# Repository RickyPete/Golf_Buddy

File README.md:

# Golf_Buddy

The Golf Buddy is a universal digital golf scorecard that can be used on any course and can be set for either 9 or 18 holes games.

Inspiration for this project came from often loosing track of strokes and forgetting to write them down on the course provided scorecards.

The goal was to develop a product that was:  
- Simple and quick to understand/use
- Comfortably fit in a pants pocket
- Lasts a single round of golf on a single charge
- Provided quick analytics of game performance

Files:

Hardware:

Instructions:

Known Issues:

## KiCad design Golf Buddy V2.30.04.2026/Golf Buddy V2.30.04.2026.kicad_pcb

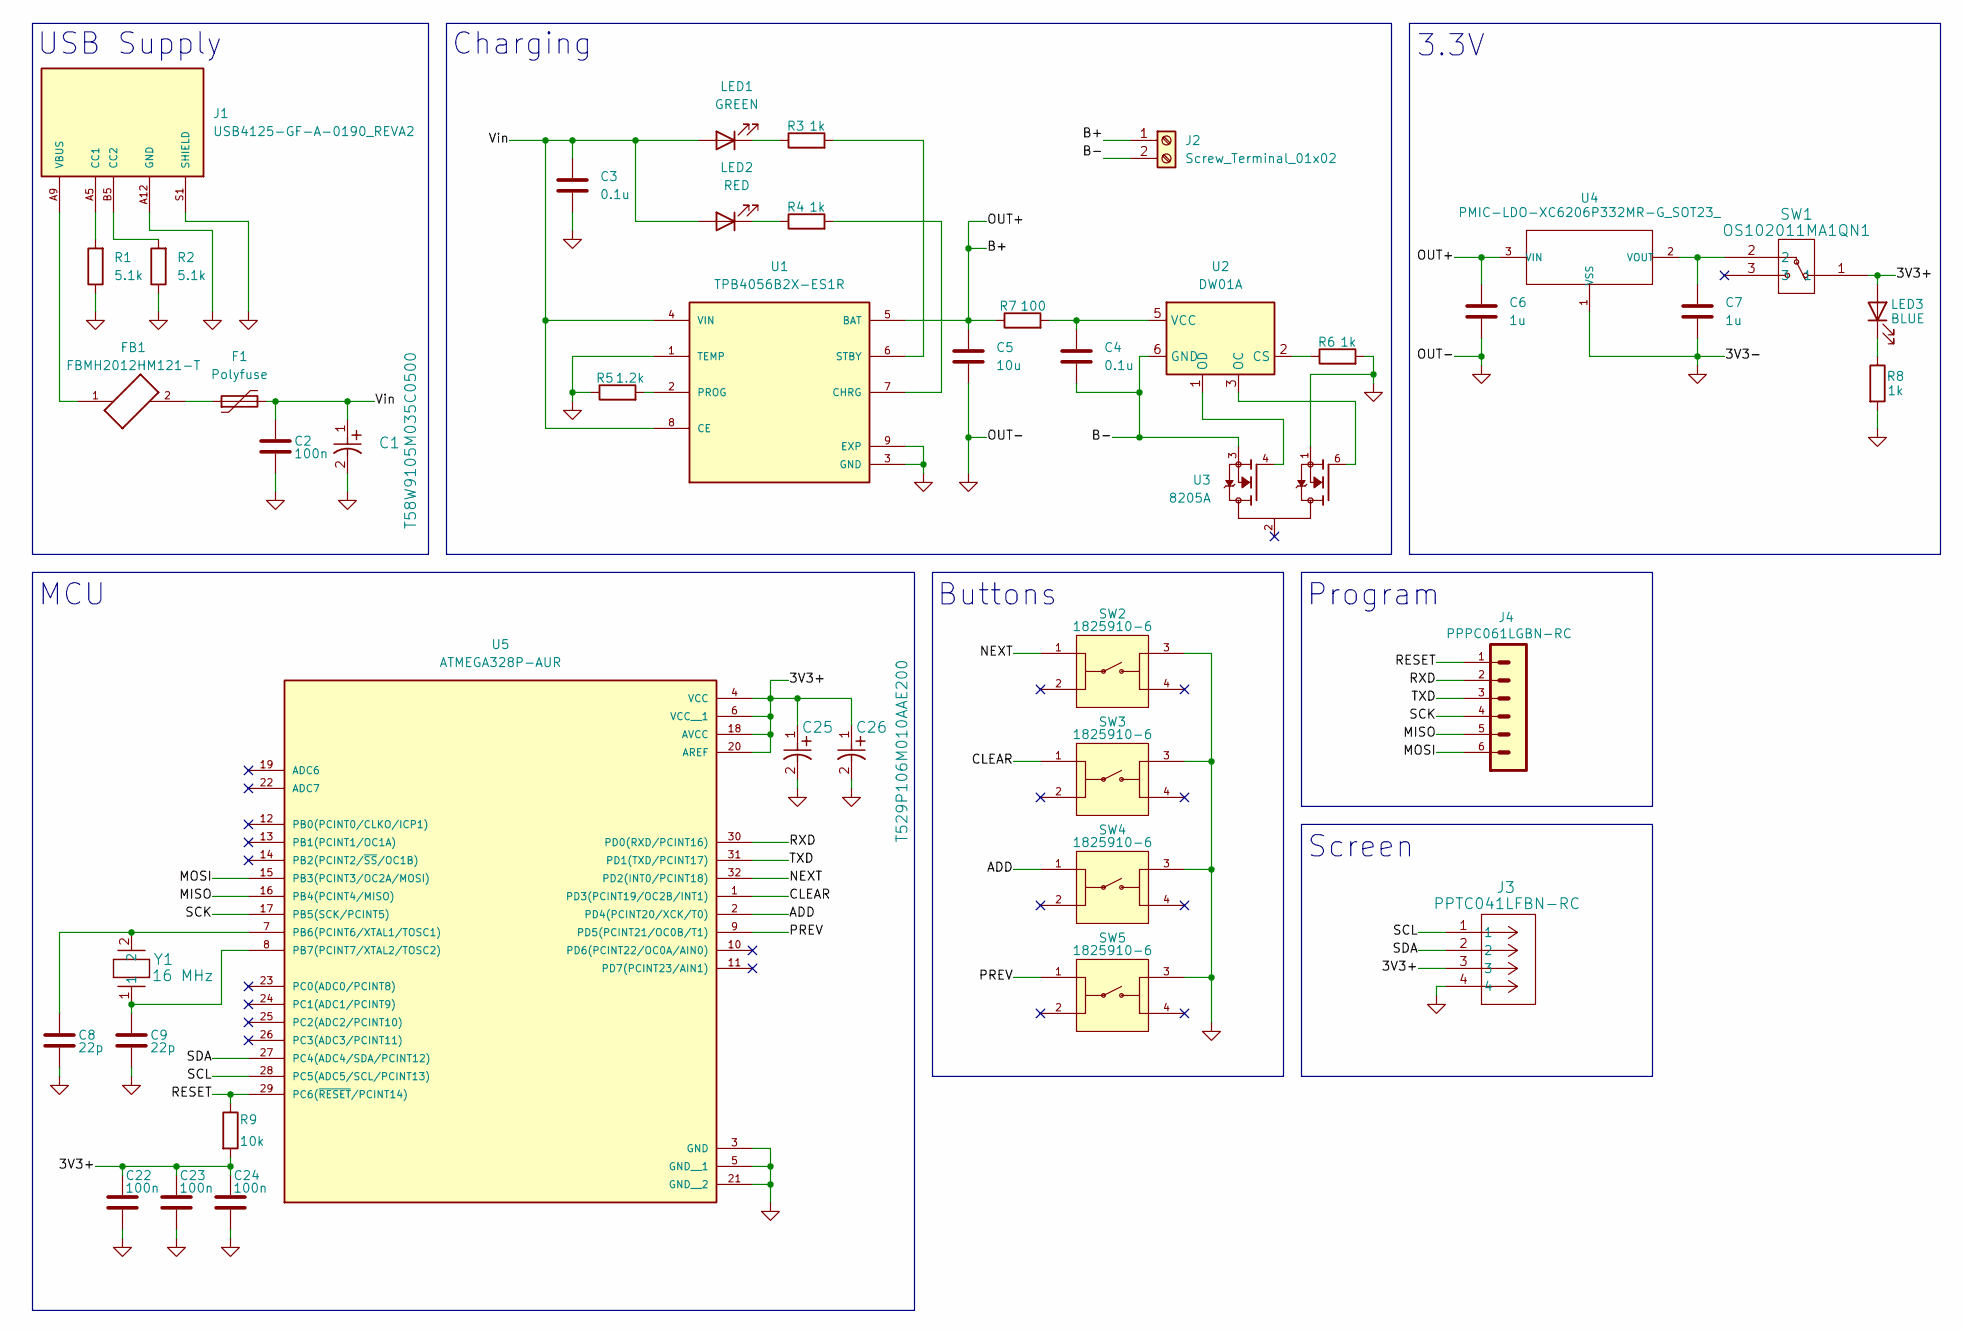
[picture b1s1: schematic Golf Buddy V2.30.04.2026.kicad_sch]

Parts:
C1: T58W9105M035C0500; PCAP_T58W9_VIS
C2, C22, C23, C24: 100n; C_0402_1005Metric
C3, C4: 0.1u; C_0402_1005Metric
C5: 10u; C_0402_1005Metric
C6, C7: 1u; C_0402_1005Metric
C8, C9: 22p; C_0402_1005Metric
C25, C26: T529P106M010AAE200; CAPMP2.1X1.25_1N_KEM
F1: Polyfuse; Fuse_0402_1005Metric
FB1: FBMH2012HM121-T; BEADC2012X105N
J1: USB4125-GF-A-0190_REVA2; GCT_USB4125-GF-A-0190_REVA2; PARTREV Rev A2; DigiKey_Part_Number 2073-USB4125-GF-A-0190CT-ND
J2: Screw_Terminal_01x02; PinHeader_1x02_P2.00mm_Vertical
J3: PPTC041LFBN-RC; CONN_PPTC041LFBN-RC_SUL
J4: PPPC061LGBN-RC; DigiKey_Part_Number S5481-ND
LED1: GREEN; LED_0603_1608Metric
LED2: RED; LED_0603_1608Metric
LED3: BLUE; LED_0603_1608Metric
R1, R2: 5.1k; R_0402_1005Metric
R3, R4, R6, R8: 1k; R_0402_1005Metric
R5: 1.2k; R_0402_1005Metric
R7: 100; R_0402_1005Metric
R9: 10k; R_0402_1005Metric
SW1: OS102011MA1QN1; OS102011MA1QN1_CNK
SW2, SW3, SW4, SW5: 1825910-6; SW_1825910-6-4; PARTREV C10; DigiKey_Part_Number 450-1650-ND
U1: TPB4056B2X-ES1R; SOIC127P600X170-9N; PARTREV A.4
U2: DW01A; SOT-23-6
U3: 8205A; SOT95P285X140-6N; PARTREV NA
U4: PMIC-LDO-XC6206P332MR-G_SOT23_; SOT-23; MPN XC6206P332MR-G
U5: ATMEGA328P-AUR; QFP80P900X900X120-32N; PARTREV A
Y1: 16 MHz; XTAL_HCM49_CIT

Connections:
/3V3+: C22.2, C23.2, C24.2, C25.1, C26.1, J3.3, LED3.2 (A), R9.2, SW1.1, U5.4 (VCC), U5.6 (VCC__1), U5.18 (AVCC), U5.20 (AREF)
/ADD: SW4.1, U5.2 (PD4(PCINT20/XCK/T0))
/B+: C5.1, C6.1, J2.1, R7.1, U1.5 (BAT), U4.3 (VIN)
/B-: C4.2, J2.2, U2.6 (GND), U3.3
/CLEAR: SW3.1, U5.1 (PD3(PCINT19/OC2B/INT1))
/MISO: J4.5, U5.16 (PB4(PCINT4/MISO))
/MOSI: J4.6, U5.15 (PB3(PCINT3/OC2A/MOSI))
/NEXT: SW2.1, U5.32 (PD2(INT0/PCINT18))
/PREV: SW5.1, U5.9 (PD5(PCINT21/OC0B/T1))
/RESET: J4.1, R9.1, U5.29 (PC6(~RESET/PCINT14))
/RXD: J4.2, U5.30 (PD0(RXD/PCINT16))
/SCK: J4.4, U5.17 (PB5(SCK/PCINT5))
/SCL: J3.1, U5.28 (PC5(ADC5/SCL/PCINT13))
/SDA: J3.2, U5.27 (PC4(ADC4/SDA/PCINT12))
/TXD: J4.3, U5.31 (PD1(TXD/PCINT17))
/Vin: C1.1, C2.1, C3.1, F1.2, LED1.2 (A), LED2.2 (A), U1.4 (VIN), U1.8 (CE)
GND: C1.2, C2.2, C3.2, C5.2, C6.2, C7.2, C8.2, C9.2, C22.1, C23.1, C24.1, C25.2, C26.2, J1.A12 (GND), J1.B12 (GND), J1.S1 (SHIELD), J1.S2 (SHIELD), J1.S3 (SHIELD), J1.S4 (SHIELD), J3.4, R1.1, R2.1, R5.1, R6.2, R8.2, SW2.3, SW3.3, SW4.3, SW5.3, U1.1 (TEMP), U1.3 (GND), U1.9 (EXP), U3.1, U4.1 (VSS), U5.3 (GND), U5.5 (GND__1), U5.21 (GND__2)
unnamed: F1.1, FB1.2
unnamed: J1.A5 (CC1), R1.2
unnamed: J1.B5 (CC2), R2.2
unnamed: LED1.1 (K), R3.1
unnamed: LED2.1 (K), R4.1
unnamed: LED3.1 (K), R8.1
unnamed: R4.2, U1.7 (CHRG)
unnamed: R5.2, U1.2 (PROG)
unnamed: R3.2, U1.6 (STBY)
unnamed: R6.1, U2.2 (CS)
unnamed: U2.3 (OC), U3.6
unnamed: U2.1 (OD), U3.4
unnamed: C4.1, R7.2, U2.5 (VCC)
unnamed: C7.1, SW1.2, U4.2 (VOUT)
unnamed: C8.1, U5.7 (PB6(PCINT6/XTAL1/TOSC1)), Y1.2
unnamed: C9.1, U5.8 (PB7(PCINT7/XTAL2/TOSC2)), Y1.1
VBUS: FB1.1, J1.A9 (VBUS), J1.B9 (VBUS)

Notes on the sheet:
Buttons
Charging
Screen
USB Supply
Program
3.3V
MCU

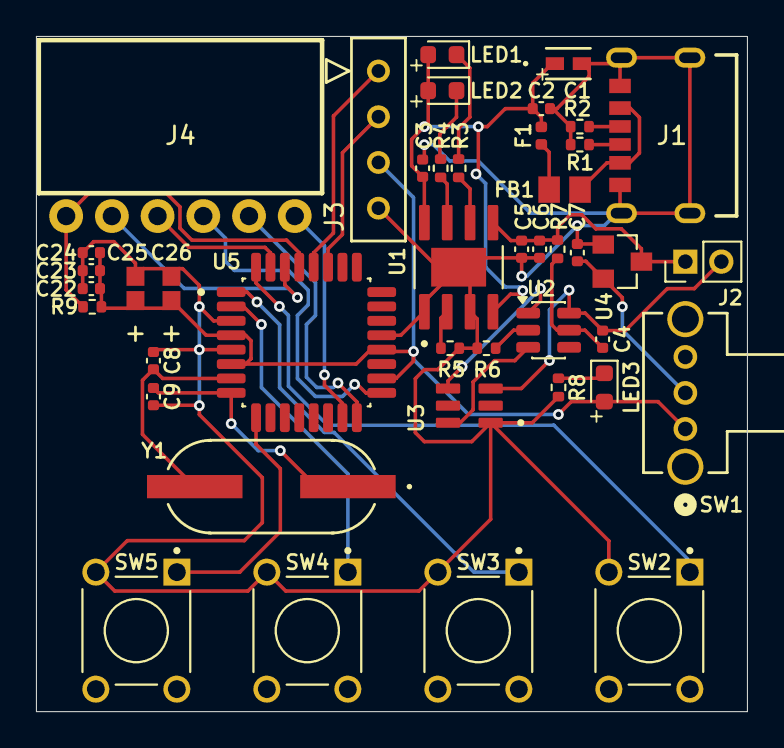
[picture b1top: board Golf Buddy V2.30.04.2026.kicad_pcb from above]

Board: 2 copper layers, 39.5 x 37.5 mm, 43 parts (0 on the bottom side), 34 nets.

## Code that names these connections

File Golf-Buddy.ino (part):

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#define SCREEN_ADDRESS      0x3C  // Updated address from 0x3D to 0x3C
Adafruit_SSD1306 display(SCREEN_WIDTH, SCREEN_HEIGHT, &Wire, OLED_RESET);

const byte buttonPins[] = {5, 4, 3, 2}; // PREV, ADD, CLEAR, NEXT

typedef enum {
  START,
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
